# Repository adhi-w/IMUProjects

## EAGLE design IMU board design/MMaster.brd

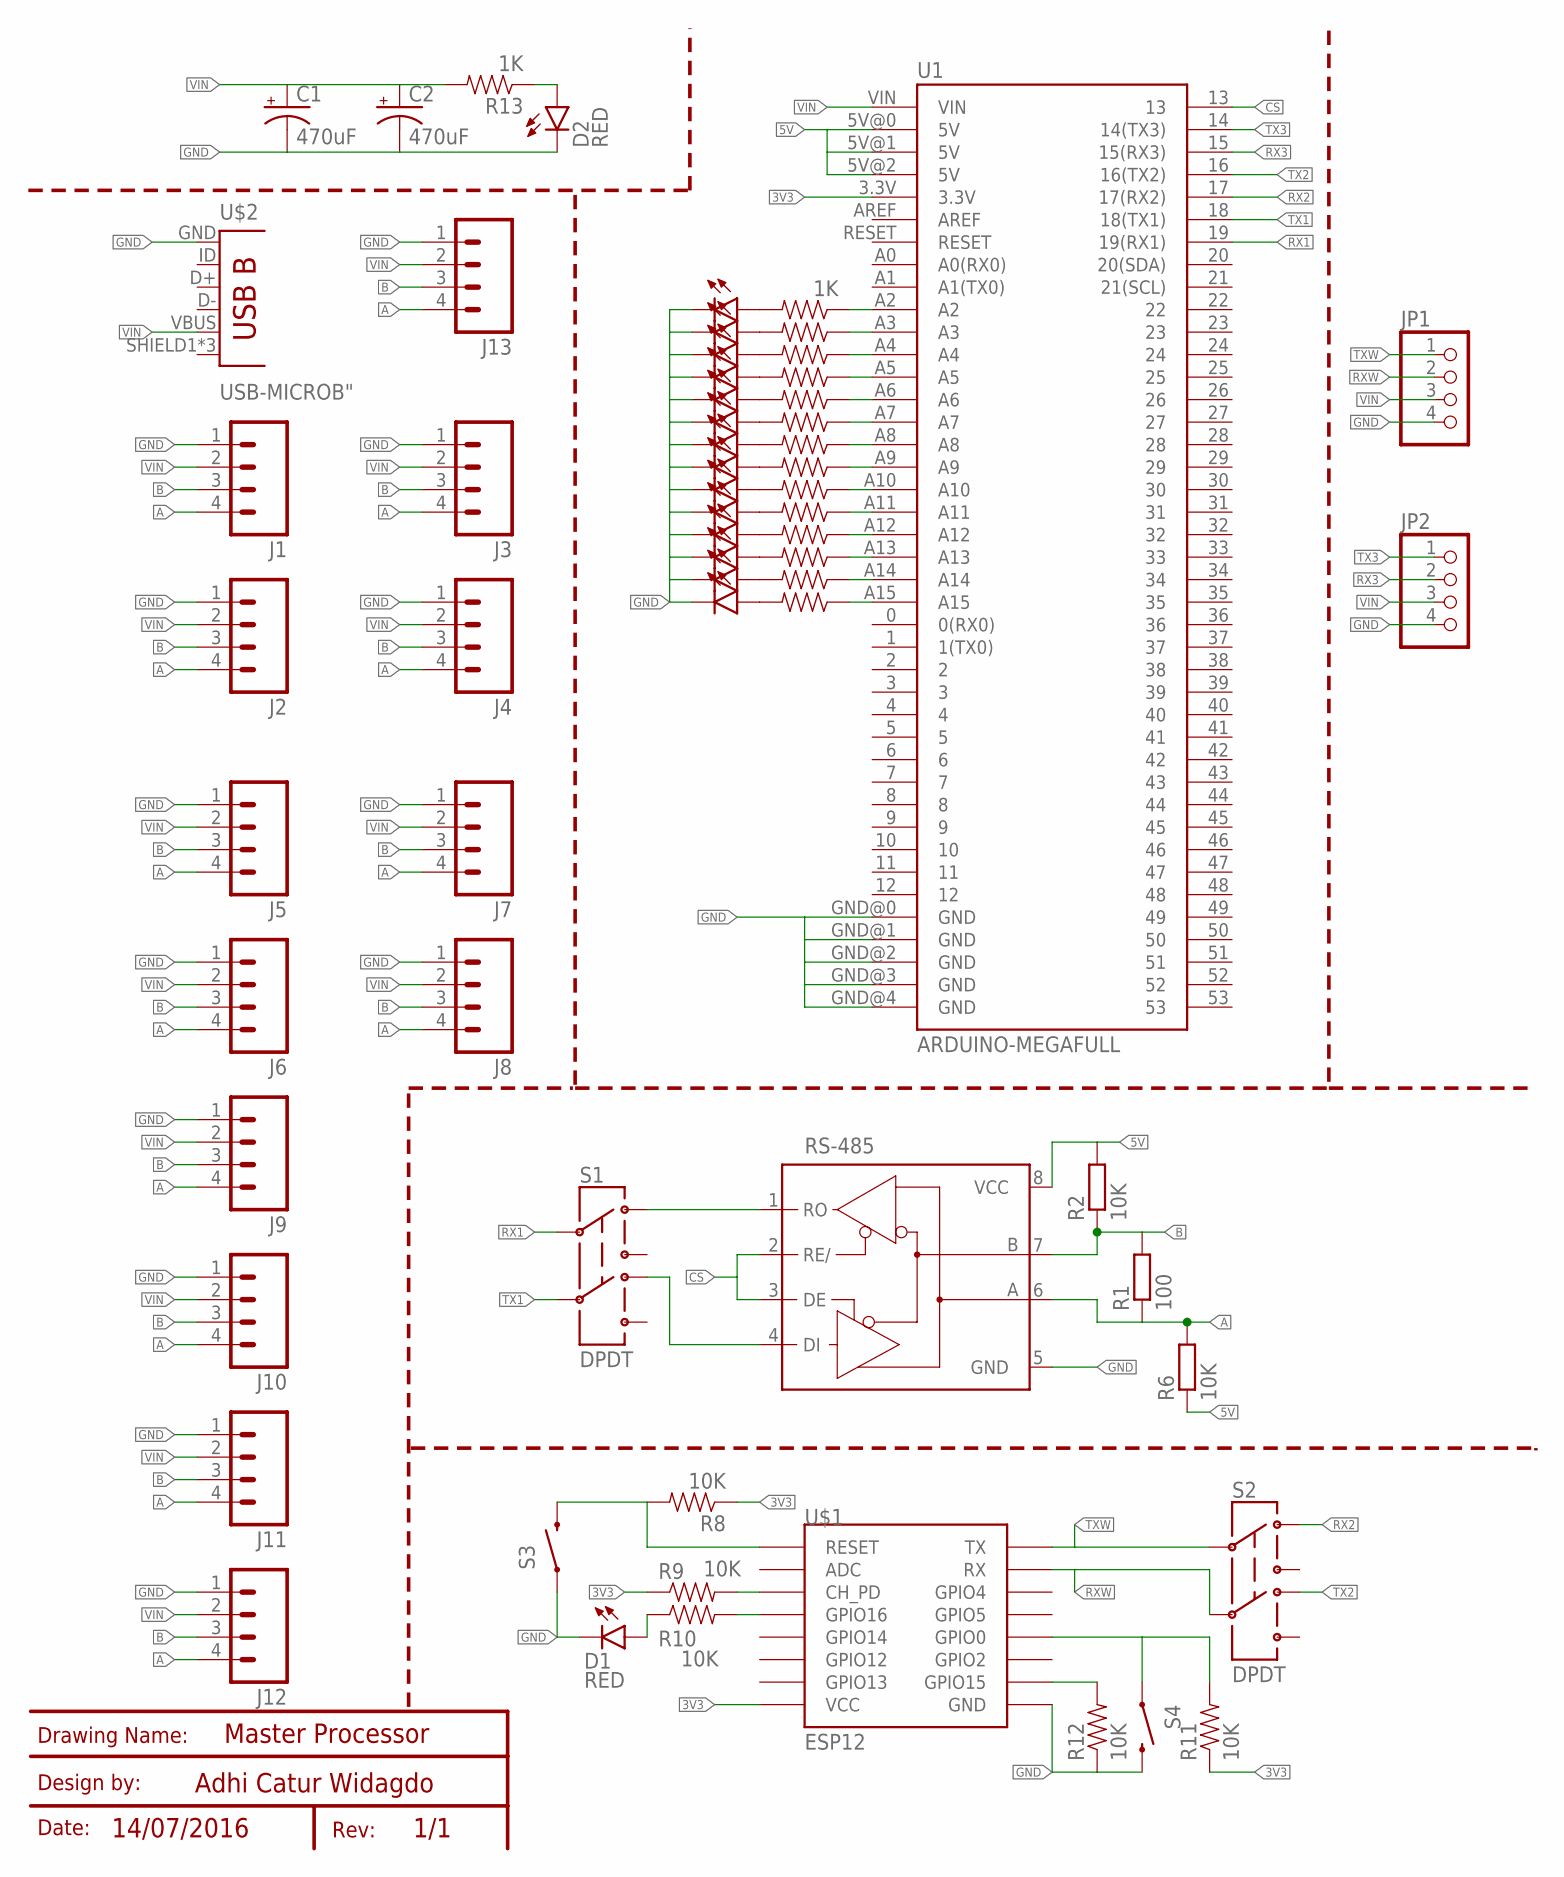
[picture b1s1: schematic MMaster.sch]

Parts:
C1, C2: 470uF; E3,5-8
D1, D2, D3, D4, D5, D6, D7, D8, D9, D10, D11, D12, D13, D14, D15, D16: RED; LED-0603
J1, J2, J3, J4, J5, J6, J7, J8, J9, J10, J11, J12, J13: M04POLAR; MOLEX-1X4
JP1, JP2: PINHD-1X4; 1X04
R1: 100; 0204/7
R2, R6: 10K; 0204/7
R8, R9, R10, R11, R12: 10K; 0603-RES
R13, R14, R15, R16, R17, R18, R19, R20, R21, R22, R23, R24, R25, R26, R27: 1K; 0603-RES
RS-485: MAX3468CPA; DIL08
S1, S2: DPDT; AYZ0202
S3, S4: SWITCH-MOMENTARY-2SMD-1101NE; TACTILE-SWITCH-1101NE
U1: ARDUINO-MEGAFULL; ARDUINO_MEGA
U$1: ESP12
U$2: USB-MICROB"; USB-B-MICRO-SMD_V03

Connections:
3V3: R8.1, R9.1, R11.1, U1.3.3V, U$1.VCC
5V: R2.2, R6.1, RS-485.8 (VCC), U1.5V@0 (5V), U1.5V@1 (5V), U1.5V@2 (5V)
A: J1.4, J2.4, J3.4, J4.4, J5.4, J6.4, J7.4, J8.4, J9.4, J10.4, J11.4, J12.4, J13.4, R1.1, R6.2, RS-485.6 (A)
B: J1.3, J2.3, J3.3, J4.3, J5.3, J6.3, J7.3, J8.3, J9.3, J10.3, J11.3, J12.3, J13.3, R1.2, R2.1, RS-485.7 (B)
CS: RS-485.2 (RE/), RS-485.3 (DE), U1.13
GND: C1.-, C2.-, D1.C, D2.C, D3.C, D4.C, D5.C, D6.C, D7.C, D8.C, D9.C, D10.C, D11.C, D12.C, D13.C, D14.C, D15.C, D16.C, J1.1, J2.1, J3.1, J4.1, J5.1, J6.1, J7.1, J8.1, J9.1, J10.1, J11.1, J12.1, J13.1, JP1.4, JP2.4, R12.1, RS-485.5 (GND), S3.1, S4.2, U1.GND@0 (GND), U1.GND@1 (GND), U1.GND@2 (GND), U1.GND@3 (GND), U1.GND@4 (GND), U$1.GND, U$2.GND
unnamed: RS-485.1 (RO), S1.1
unnamed: RS-485.4 (DI), S1.4
unnamed: R12.2, U$1.GPIO15
unnamed: R10.2, U$1.GPIO16
unnamed: R11.2, S4.1, U$1.GPIO0
unnamed: D1.A, R10.1
unnamed: R8.2, S3.2, U$1.RESET
unnamed: R9.2, U$1.CH_PD
unnamed: D2.A, R13.1
unnamed: R27.1, U1.A15
unnamed: R26.1, U1.A14
unnamed: R25.1, U1.A13
unnamed: R24.1, U1.A12
unnamed: R23.1, U1.A11
unnamed: R22.1, U1.A10
unnamed: R21.1, U1.A9
unnamed: R20.1, U1.A8
unnamed: R19.1, U1.A7
unnamed: R18.1, U1.A6
unnamed: R17.1, U1.A5
unnamed: R16.1, U1.A4
unnamed: R15.1, U1.A3
unnamed: R14.1, U1.A2
unnamed: D3.A, R14.2
unnamed: D4.A, R15.2
unnamed: D5.A, R16.2
unnamed: D6.A, R17.2
unnamed: D7.A, R18.2
unnamed: D8.A, R19.2
unnamed: D9.A, R20.2
unnamed: D10.A, R21.2
unnamed: D11.A, R22.2
unnamed: D12.A, R23.2
unnamed: D13.A, R24.2
unnamed: D14.A, R25.2
unnamed: D15.A, R26.2
unnamed: D16.A, R27.2
RX1: S1.2, U1.19 (19(RX1))
RX2: S2.1, U1.17 (17(RX2))
RX3: JP2.2, U1.15 (15(RX3))
RXW: JP1.2, S2.5, U$1.RX
TX1: S1.5, U1.18 (18(TX1))
TX2: S2.4, U1.16 (16(TX2))
TX3: JP2.1, U1.14 (14(TX3))
TXW: JP1.1, S2.2, U$1.TX
VIN: C1.+, C2.+, J1.2, J2.2, J3.2, J4.2, J5.2, J6.2, J7.2, J8.2, J9.2, J10.2, J11.2, J12.2, J13.2, JP1.3, JP2.3, R13.2, U1.VIN, U$2.VBUS

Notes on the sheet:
Drawing Name:
Design by:
Date:
Rev:
Master Processor
Adhi Catur Widagdo
14/07/2016
1/1

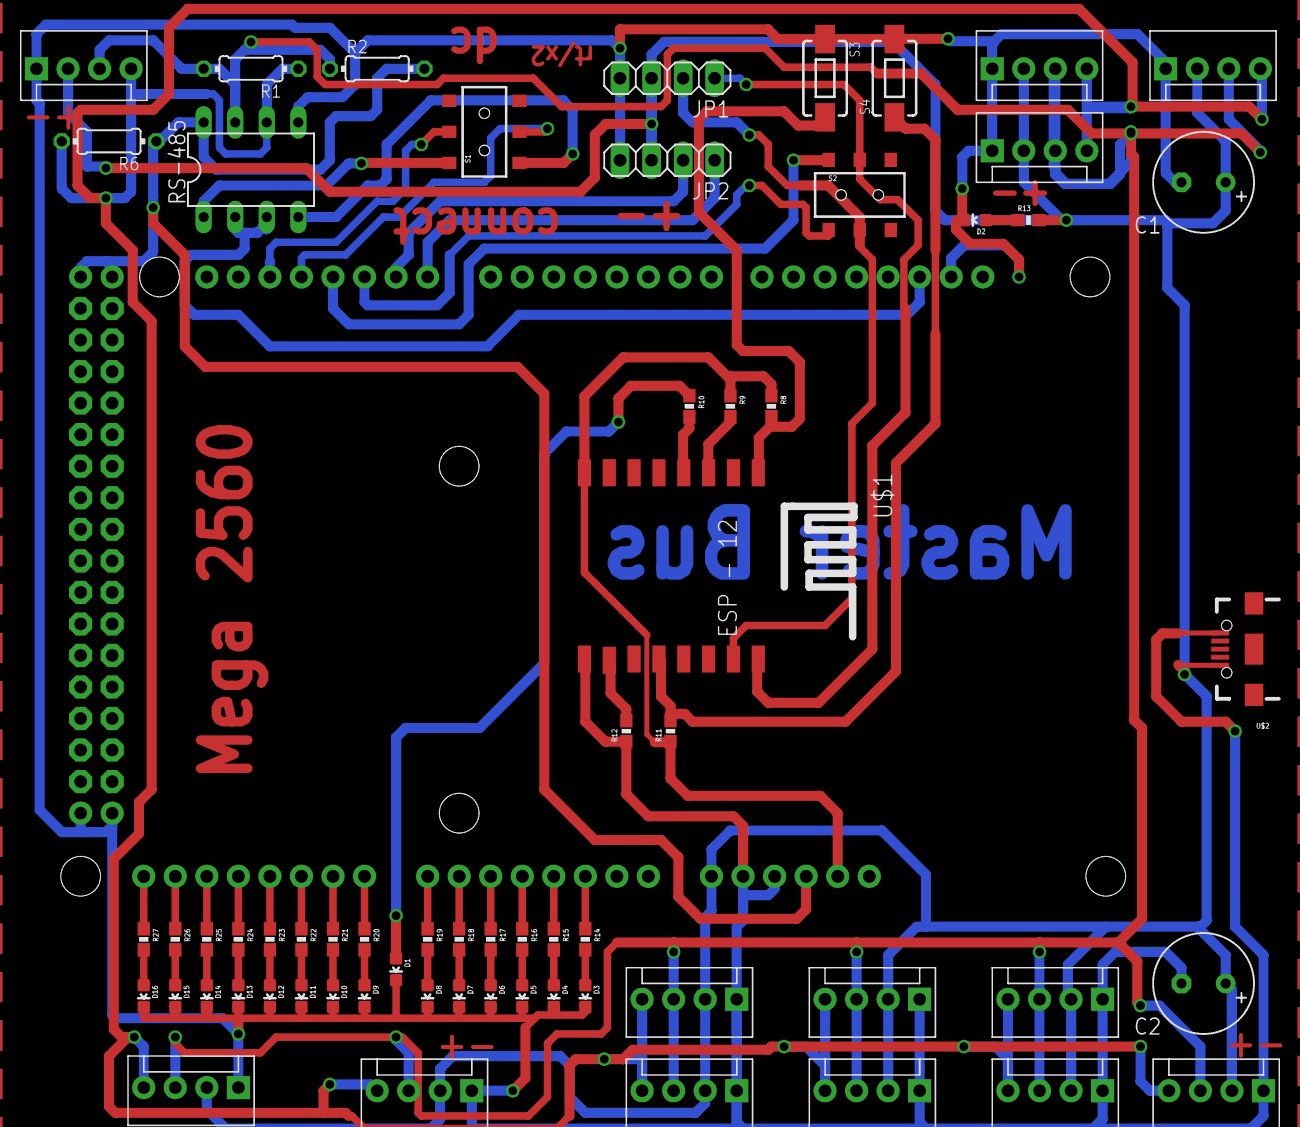
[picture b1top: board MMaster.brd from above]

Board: 2 copper layers, 64 parts (1 on the bottom side), 52 nets.

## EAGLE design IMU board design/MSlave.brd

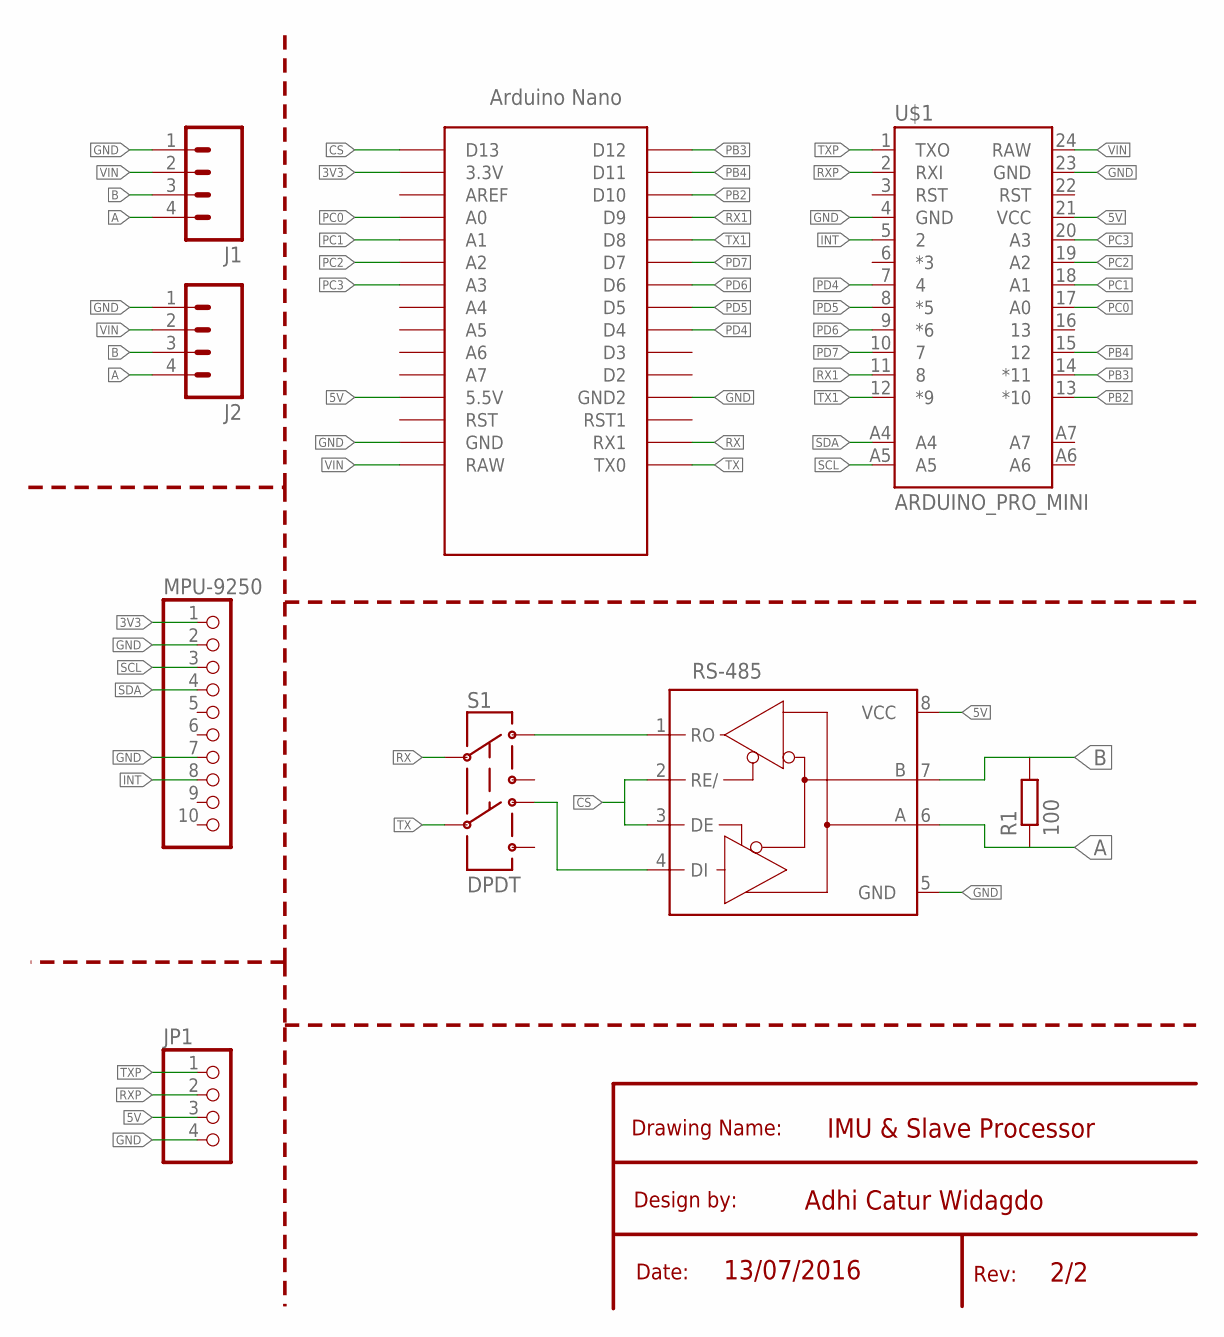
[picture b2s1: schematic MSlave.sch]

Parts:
J1, J2: M04POLAR; MOLEX-1X4
JP1: PINHD-1X4; 1X04
MCU_SLAVE: MCU_Slave; NANO
MPU-9250: PINHD-1X10; 1X10
R1: 100; 0204/7
RS-485: MAX3468CPA; DIL08
S1: DPDT; AYZ0202
U$1: ARDUINO_PRO_MINI

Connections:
3V3: MCU_SLAVE.3.3V, MPU-9250.1
5V: JP1.3, MCU_SLAVE.5V (5.5V), RS-485.8 (VCC), U$1.21 (VCC)
A: J1.4, J2.4, R1.1, RS-485.6 (A)
B: J1.3, J2.3, R1.2, RS-485.7 (B)
CS: MCU_SLAVE.D13, RS-485.2 (RE/), RS-485.3 (DE)
GND: J1.1, J2.1, JP1.4, MCU_SLAVE.GND, MCU_SLAVE.GND1 (GND2), MPU-9250.2, MPU-9250.7, RS-485.5 (GND), U$1.4 (GND), U$1.23 (GND)
INT: MPU-9250.8, U$1.5 (2)
unnamed: RS-485.1 (RO), S1.1
unnamed: RS-485.4 (DI), S1.4
PB2: MCU_SLAVE.D10, U$1.13 (*10)
PB3: MCU_SLAVE.D12, U$1.14 (*11)
PB4: MCU_SLAVE.D11, U$1.15 (12)
PC0: MCU_SLAVE.A0, U$1.17 (A0)
PC1: MCU_SLAVE.A1, U$1.18 (A1)
PC2: MCU_SLAVE.A2, U$1.19 (A2)
PC3: MCU_SLAVE.A3, U$1.20 (A3)
PD4: MCU_SLAVE.D4, U$1.7 (4)
PD5: MCU_SLAVE.D5, U$1.8 (*5)
PD6: MCU_SLAVE.D6, U$1.9 (*6)
PD7: MCU_SLAVE.D7, U$1.10 (7)
RX: MCU_SLAVE.RX1, S1.2
RX1: MCU_SLAVE.D9, U$1.11 (8)
RXP: JP1.2, U$1.2 (RXI)
SCL: MPU-9250.3, U$1.A5
SDA: MPU-9250.4, U$1.A4
TX: MCU_SLAVE.TX0, S1.5
TX1: MCU_SLAVE.D8, U$1.12 (*9)
TXP: JP1.1, U$1.1 (TXO)
VIN: J1.2, J2.2, MCU_SLAVE.RAW, U$1.24 (RAW)

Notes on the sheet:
Drawing Name:
Design by:
Date:
Rev:
IMU & Slave Processor
Adhi Catur Widagdo
13/07/2016
2/2

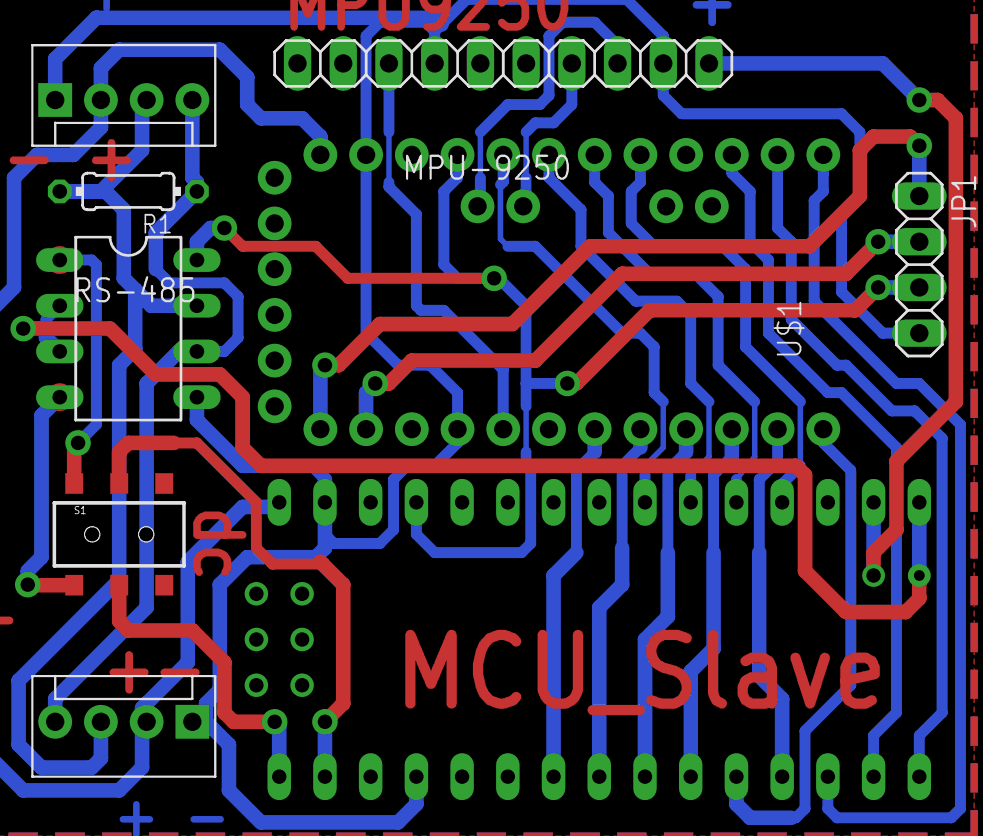
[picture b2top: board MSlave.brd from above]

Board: 2 copper layers, 9 parts (0 on the bottom side), 29 nets.

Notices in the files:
parts and their libraries:
SparkFun-Electromechanical: Licensing: Creative Commons ShareAlike 4.0 International - https://creativecommons.org/licenses/by-sa/4.0
